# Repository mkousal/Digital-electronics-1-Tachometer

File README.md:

# DIGITAL ELECTRONICS 1
**2021**, Faculty of Electrical Engineering and Communication [FEKT](https://www.fekt.vut.cz/) <br/> 
 <br/>
**Title:** Project 2021 <br/>
**Topic:** 3. Console for bike with hall sensor, measuring and displaying speed, traveled distance and burnt calories <br/>
**Time Window:** 
   - *Start of Project*: *April 7*
   - *End of Project*:   *May 4* <br/>

**Supervisor:** **_doc. Ing. Tomáš Frýza, Ph.D._** <br/>
**Vivado Teachers:** **_doc. Ing. Tomáš Frýza, Ph.D._**, **_Ing. Stanislav Rozum_**

# 3. Console for bike with hall sensor, measuring and displaying speed, traveled distance and burnt calories

### Team members

- **Martin Kousal**, **ID=** *221063* <br/> 
[Link to GitHub project folder]( http://github.com/mkousal/Digital-electronics-1-Tachometer) <br/> 
- **Matej Ledvina**, **ID=** *221339* <br/> 
[Link to GitHub]( https://github.com/Ledvuk/Digital-electronics-1) <br/> 
- **Tomáš Kříčka**, **ID=**  *223283* <br/> 
[Link to GitHub]( https://github.com/TomasKricka) <br/> 
- **Samuel Košík**, **ID=** *221056* <br/>
[Link to GitHub project folder]( https://github.com/amwellius/Digital-electronics-1/tree/main/Labs/project)

### Project objectives

Our application uses two hall sensors for measuring speed, traveled distance, burnt calories and time (not by the hall sensor). <br/>
This data is shown on four 7segment displays (one part).
  - Calories counting
  - Total time
  - Total distance traveled
  - Trip distance traveled
  - Speed measuring <br/>

Modes can be selected by pressing buttons (see below). <br/>
One hall sensor is used for measuring speed and traveled distance. Another one is for calories counting. <br/>
Burnt calories will increase only by stepping the pedals, not by downhill riding!

## Hardware description

   ### Programming Board
   
   - Main programming board is **Arty A7-100T**. It has four Pmod connectors (16.), we have used all of them
   - Other buttons and LEDs are not used => See **Main Board**

   ### Main Board

   - [Schematic](files/tachometerBoard_schematic.pdf)
   - **Consists of:** three buttons, 7segment display, Pmod connectors, LED status and two connectors for Hall sensors
   - Board is made for direct connection to Arty A7 board. Three buttons are used to controlling the tachometer. LED at the top shows what value is now displayed at the display
   - Used seven segment display with middle double dot and dots for decimal is TDCG1050m - [datasheet](https://www.vishay.com/docs/83180/tdcx10x0m.pdf)

   ### Hall sensor board

   - [Schematic](files/encoderBoard_schematic.pdf)
   - Hall sensor board only consists of hall sensor and a few passive components that are described in datasheet and connector
   - You can screw it by using M3 screw to your bicycle
   - Used sensor is *MH253* - [datasheet](https://datasheet.lcsc.com/szlcsc/1811141821_MST-Magnesensor-Tech-MST-MH253ESO_C114369.pdf)

## VHDL modules description

### Buttons
#### `Button_int`:
   - This block reads the input from real world buttons and translates them to commands which will be sent to the state_machine controller. When buttons *up* or *down* are            pressed, the interface will enter a cooldown state when no additional button presses will be registered (to prevent jitter) after the cooldown passes, the interface will        send an *up* or *down* command out
   - If the *ok* button is pressed, the device enters the cooldown state, after which it will wait for a longer ammount of time. If no additional *ok* button press is                registered, the interface will send out an *startstop* command
   - If, however, the *ok* button would be pressed again, the interface will send out the *reset* command
### Traveled distance
#### `km_total`:
   - This block counts the travel distance and sends it out to the display. Every 100 m (meters) an pulse will appear on the `meters_i` which will add to the total count of up        to *999,9 km* 
   - When the **trip mode** is activated the block will count the trip time and send it to the display instead, the total time is being still counted in the background
   - *rst signal* will make the current displayed data reset to 0 
   - The enable signal will be present if the trip is not paused, on *pause* the trip data is not counted
   - This block automaticaly wipes previous trip data when the mode is turned on

This block also contains a **function** which converts the traveled distance from *binary integer* to *BCD code* to be displayed on the 4 digit 7 segment display.

### Main controling module
#### `state_machine`:
   - This is the main utility block of the device. It recives commands from the button interface and switches the outputs accordingly. Inputs `up_i` and `down_i` will cycle          through the 4 modes of the device and light up their status LED 
   - While in a mode the *data stream* from its block will be sent to be displayed on the segment display via the `data_o`, with added decimal point or double dot if needed 
   - While in a mode the *reset* and *ok* commands also aply for the selected block only. The *trip mode* is special, because it does not generate data on its own, when              activated, it will send a mode change command to all blocks which will now store and display data in an additional variable as well as keeping the total count going 
   - The status LED of trip will remain on as we cycle through the other modes until it is paused by the *startstop* button or turned off via the reset. At this point all trip        data will be reset from all blocks and the normal total data will be displayed

### Time mode
#### `total_time`:
   - This block acts as a stopwatch. When startstop is applied, it will *start* or *pause* the counting
   - *Reset* will reset the total time
   - When the *trip mode* is enabled, the stopwatch will automatically start counting the trip time and will reset before every trip is started 
 
 This block also contains a **function** which converts the total time from *binary integer* to *BCD code* to be displayed on the 4 digit 7 segment display.

### SENSOR <br/>
#### `sensor`:
   - This block is used to calculate actual speed and triggering pulse every 100 meters for counting travelled distance <br/>
   - Uses input from hall sensor mounted at the front wheel. Output one trigger signal every counted 100 meters and calculate actual real speed and set it to display output   

### 7 Segment Driver Module <br/>
   - This block consists of 4 smaller modules: 
      1. `CLOCK`
      2. `UP_DOWN_COUNTER`
      3. `DRIVER_4X7SEG`
      4. `DECODER_7SEG` <br/>
#### `CLOCK`:
   - Generates 100MHz clock
   - This periodic signal is used in module `UP_DOWN_COUNTER`, which reacts on rising edge of the signal <br/>
   - Originally uses 4ms for each segment
#### `UP_DOWN_COUNTER`:
   - According settings (g_CNT_WIDTH), counts as the edge of the clock signal rises <br/>
#### `DRIVER_4X7SEG`:
   - Main module, drives four 7segment displays. It is determinated by `CLOCK` and `UP_DOWN_COUNTER` <br/>
   - Process MUX uses above modules to set data_outputs to each 7segment display <br/>
   - Input is a 16bit unsigned (`b"xxxx xxxx xxxx xxxx"`)
#### `DECODER_7SEG`:
   This module is used for displaying data on 7segment display. If have more displays, MUX has to be used <br/>
   Both, common cathode and common anode can be used as well

### Calories Mode
#### `calories`:
   - This block calculates burned calories by measuring the time between each pedals rotations 
   - Rotation is captured by hall probe attached to pedal
   - The 100 MHz clock is used for counting time. Every 0.5s a number is increased, which recalculates the calories formula 
   - When signal from hall probe is not generating for 2s, the number that was increasing is stopped. The amount of burned calories is sent to display
   
## Testbenches and simulations
#### `Button_int`:
   - Shows states of `button_int` block
   - In order to save time and make the inner working of this device more clear, all simulated data has been sped up  

#### `km_total`:
   - Screenshot demos how the counting works
   - In order to save time and make the inner working of this device more clear, all simulated data has been sped up

#### `state_machine`:
   - Screenshot below represents testbench of main unit
   - In order to save time and make the inner working of this device more clear, all simulated data has been sped up 

#### `total_time`:
   - Funcionality of total time counting is shown by this signals
   - In order to save time and make the inner working of this device more clear, all simulated data has been sped up

#### `sensor`: <br/>
   - First waveform shows how the speed calculation works. Calculated speed is written to the `s_disp_o`, which is 16bit word and is here until the new value is calculated
   
   - Second waveform shows pulsing at the `s_trigger_o` every 50 sensor's tick, which is equal to the 100 meters in real distance

#### `CLOCK`: <br/>
   - Generates 100 MHz clock signal

#### `UP_DOWN_COUNTER`: <br/>
   - As internal values set, counts with edge of the clock
   - 0-31 states:
   
   - 0-31 states:
   
   - 0-4 states = This is used in our application
   - Four 7segment displays are controlled by this states

#### `DRIVER_4X7SEG`:
   - These screenshots show how the multiplexer works
   - `s_data` is the main 16bit data input
   - `s_hex` is the 4bit data output, which is used in `DECODER_7SEG`. This module decodes the 4bit data value and diplays it on a specific 7segment display
   - `s_dig_o` shows which one of four displays is being used. `b"0001"` means display on very right side
   - `s_seg_o` represents common cathode bits

   - This screenshot shows a real situation, when input data will be refreshed every one second (tachometer)
   - If data is not changed for a while, displays will use last data. This prevents from wrong/unwanted values
   
#### `DECODER_7SEG`:
   - Decodes 4bit signal to 7bit (7 segments (+ decimal dot and colon))

#### `calories`:
   - The simulation is in ratio 1s = 10ms
   - In wave form is display calories counting in both modes and amount of burned calories is sending to display

## TOP module description and simulations
   - TOP module represents the whole project
   - Final test schema can be seen below:
   
   - After having **main board** and **hall sensor board** done, software can be written into Arty A7 board. Generated bitstream is available [here](sw/tachometer/tachometer.runs/impl_1/top.bit). <br/>

## Video

Video presentation is available [here](https://youtu.be/21QbKaQYVqw).

## References

   ### Used materials:
   - Theoretical knowledge from Digital-Electronics-1 Labs, 2021 > [Link]( https://github.com/tomas-fryza/Digital-electronics-1/tree/master/Labs)
   - Labs from classes **DE1** 
   - DE1 Lecture PDF > [Link]( https://moodle.vutbr.cz/pluginfile.php/331523/mod_resource/content/3/DE1_lecture_part4_CZE.pdf)
   - [7 Segment Display]( https://docs.rs-online.com/6e0e/0900766b8130126b.pdf)
   - [Hall sensor](https://datasheet.lcsc.com/szlcsc/1811141821_MST-Magnesensor-Tech-MST-MH253ESO_C114369.pdf)
 
   ### Used programs and its links:
   - [Xilinx Vivado 2020]( https://www.xilinx.com/products/design-tools/vivado.html)
   - [VSCode]( https://code.visualstudio.com/)
   - [KiCad]( https://www.kicad.org/)
   - [EdaPlayGround]( https://www.edaplayground.com/)
   - [Vivado tutorials]( https://vhdlwhiz.com/basic-vhdl-tutorials/ )
   - [Tutorial from Xilinx]( https://www.xilinx.com/support/documentation/university/Vivado-Teaching/HDL-Design/2013x/Nexys4/Verilog/docs-pdf/Vivado_tutorial.pdf)
   - [Board Editor]( https://jamboard.google.com/)
   - [GitHub Desktop]( https://desktop.github.com/)
   - [Git Bash]( https://git-scm.com/download/win)
   
________________________________________________________________________________
©2021, VUT FEKT, Brno, Czech Republic <br/>
Kousal Martin, Ledvina Matej, Kříčka Tomáš, Košík Samuel <br/>
**For Educational Purposes Only!**

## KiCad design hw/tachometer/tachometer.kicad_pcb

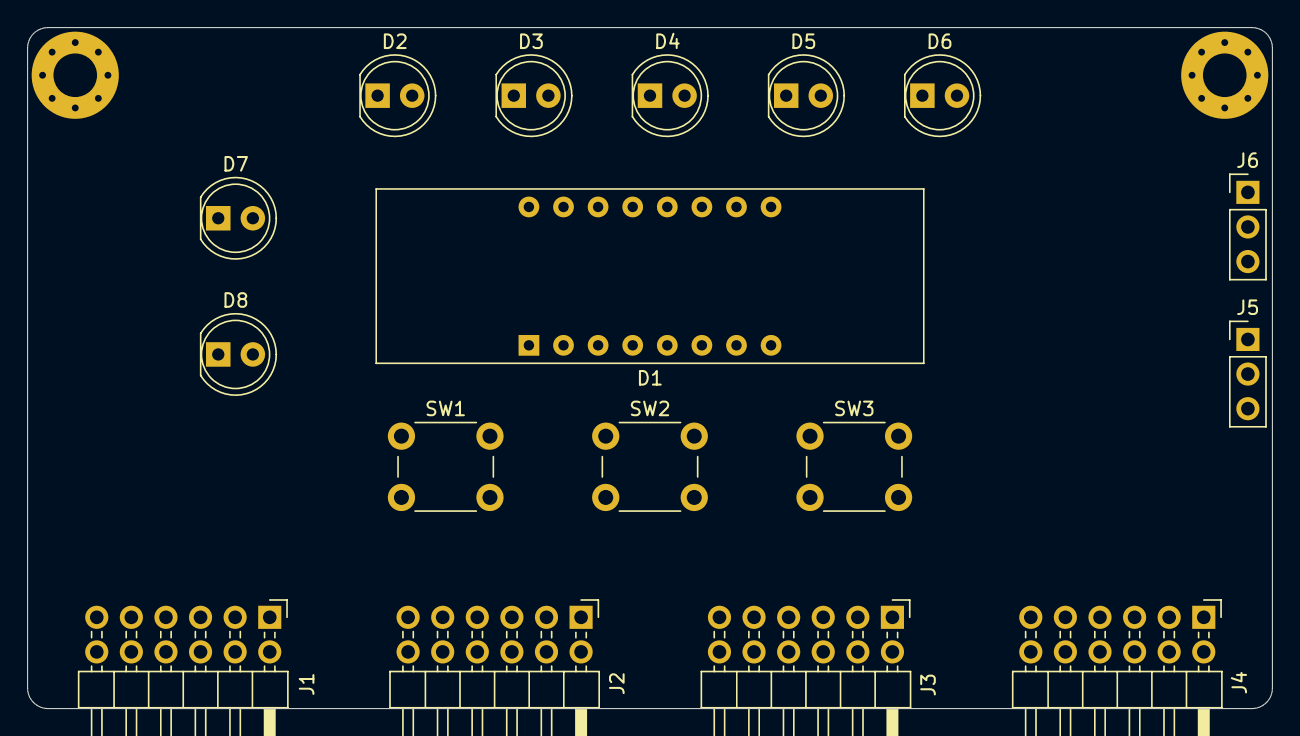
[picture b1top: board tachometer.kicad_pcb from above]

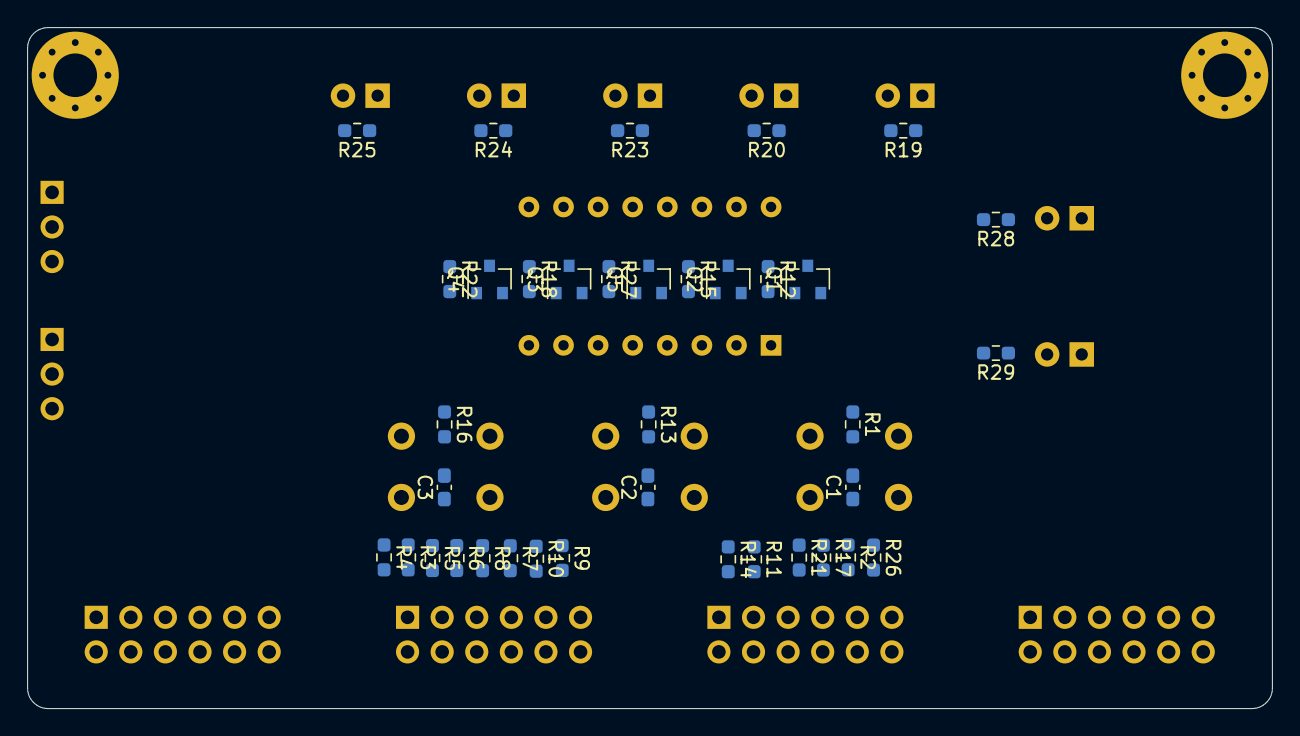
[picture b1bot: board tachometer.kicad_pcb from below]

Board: 2 copper layers, 91.4 x 50.0 mm, 54 parts (37 on the bottom side), 54 nets, no tracks yet.

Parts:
C1, C2, C3: 100n; C_0603_1608Metric_Pad1.08x0.95mm_HandSolder
D1: TDCG1050m; TDCG10..m
D2, D3, D4, D5, D6, D7, D8: LED; LED_D5.0mm
J1: Pmod JA; PinHeader_2x06_P2.54mm_Horizontal
J2: Pmod JB; PinHeader_2x06_P2.54mm_Horizontal
J3: Pmod JC; PinHeader_2x06_P2.54mm_Horizontal
J4: Pmod JD; PinHeader_2x06_P2.54mm_Horizontal
J5: HallSensor1; PinHeader_1x03_P2.54mm_Vertical
J6: HallSensor2; PinHeader_1x03_P2.54mm_Vertical
Q1, Q2, Q3, Q4, Q5: BC817; SOT-23
R1, R12, R13, R15, R16, R18, R22, R27: 10k; R_0603_1608Metric_Pad0.98x0.95mm_HandSolder
R2, R3, R4, R5, R6, R7, R8, R9, R10, R19, R20, R23, R24, R25, R28, R29: 220; R_0603_1608Metric_Pad0.98x0.95mm_HandSolder
R11, R14, R17, R21, R26: 1k5; R_0603_1608Metric_Pad0.98x0.95mm_HandSolder
SW1, SW2, SW3: SW_Push_Dual; SW_PUSH_6mm

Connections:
A11: C3.2, J1.7, R16.2, SW3.1
A18: J1.8, R24.1
B11: C2.2, J1.9, R13.2, SW2.1
B18: J1.10, R23.1
C15: J2.5, R14.2
D12: J1.5, R19.1
D13: J1.12, R20.1
D15: J2.7, R11.2
E15: J2.11, R28.1
E16: J2.9, R29.1
G2: J4.6, J5.3
G13: C1.2, J1.11, R1.2, SW1.1
GND: C1.1, C2.1, C3.1, D2.1, D3.1, D4.1, D5.1, D6.1, D7.1, D8.1, J1.3, J1.4, J2.3, J2.4, J3.3, J3.4, J4.3, J4.4, J5.1, J6.1, R12.1, R15.1, R18.1, R22.1, R27.1, SW1.2, SW2.2, SW3.2
H2: J4.8, J6.3
J15: J2.6, R2.2
J17: J2.12, R17.2
J18: J2.10, R21.2
K15: J2.8, R26.2
K16: J1.6, R25.1
unnamed: D1.3, R5.1
unnamed: D1.5, R6.1
unnamed: D1.7, R9.1
unnamed: D1.11, R7.1
unnamed: D1.12, R10.1
unnamed: D1.13, R4.1
unnamed: D1.14, R2.1
unnamed: D1.15, R8.1
unnamed: D1.16, R3.1
unnamed: D2.2, R19.2
unnamed: D3.2, R20.2
unnamed: D4.2, R23.2
unnamed: D5.2, R24.2
unnamed: D6.2, R25.2
unnamed: D7.2, R28.2
unnamed: D8.2, R29.2
unnamed: Q1.1, R11.1, R12.2
unnamed: Q2.1, R14.1, R15.2
unnamed: Q3.1, R17.1, R18.2
unnamed: Q4.1, R21.1, R22.2
unnamed: Q5.1, R26.1, R27.2
SEG_1: D1.1, Q1.2
SEG_2: D1.2, Q2.2
SEG_3: D1.6, Q3.2
SEG_4: D1.8, Q4.2
SEG_5: D1.4, Q5.2
T13: J3.8, R9.2
U12: J3.11, R3.2
U13: J3.6, R10.2
U14: J3.12, R7.2
V10: J3.7, R5.2
V11: J3.5, R6.2
V12: J3.9, R4.2
V14: J3.10, R8.2
VCC: J1.1, J1.2, J2.1, J2.2, J3.1, J3.2, J4.1, J4.2, J5.2, J6.2, Q1.3, Q2.3, Q3.3, Q4.3, Q5.3, R1.1, R13.1, R16.1

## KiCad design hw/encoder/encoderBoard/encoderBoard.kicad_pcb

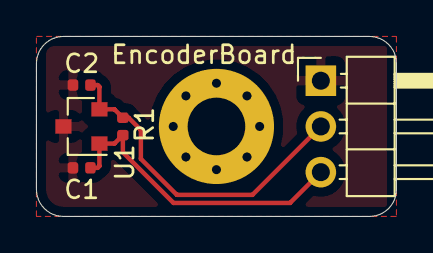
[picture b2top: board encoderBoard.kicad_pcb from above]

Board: 2 copper layers, 20.0 x 10.0 mm, 5 parts (0 on the bottom side), 3 nets.

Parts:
C1: 10n; C_0402_1005Metric
C2: 100p; C_0402_1005Metric
J1: Conn_01x03; PinHeader_1x03_P2.54mm_Horizontal
R1: 10k; R_0402_1005Metric
U1: MH253; SOT-23

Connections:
GND: C1.2, C2.2, J1.1, U1.3
unnamed: C2.1, J1.2, R1.2, U1.2
VCC: C1.1, J1.3, R1.1, U1.1

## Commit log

2021-04-07 Create Vivado project
2021-04-08 Create encoderBoard
2021-04-09 add block_schema
2021-04-14 Add tachometer board and schematic before routing
2021-04-15 Swap pinhead pinout, add GND polygon to bottom
2021-04-18 Created Readme.md
2021-04-29 Added images
2021-05-01 Added 7seg files
2021-05-01 Final routing boards
2021-05-01 Add board images
2021-05-01 Update README
    Add HW descriptions and board render images
2021-05-01 Add schematics in PDF of boards
2021-05-02 Import files to Vivado project
2021-05-02 commented sensors file, resolved some errors
2021-05-02 Update README.md
    Add a description of sensor block and testbenches of it
2021-05-02 Add testbench images of sensor module
2021-05-02 Imported all needed blocks and testbenches to Vivado
2021-05-02 Add waveforms and update README (modul calories)
2021-05-02 Finalize top module, implementation successfull
2021-05-03 My commit
    Descriptions and simulation screenshots from my blocks
2021-05-03 Update README.md
    added my ID and github link
2021-05-03 add top schemas
2021-05-03 tb_UP_DOWN_COUNTER_0-3
2021-05-03 Update README.md
    gramatika
2021-05-03 add repaired pictures of top
2021-05-03 Add newer render of main board, add generated bitstream from Vivado
2021-05-03 Update README.md
    Change '\' to '/' in bitstream link
2021-05-03 Update README.md
    Removed duplicate Vivado links
2021-05-03 add repaired top schema
2021-05-03 Update README.md
    Added video presentation link
2021-05-03 Generated README.pdf
2021-05-04 Change relative links to absolute in README
